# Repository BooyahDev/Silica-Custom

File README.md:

# SiliCa Custom — 4カード切替版

[19AJ137/SiliCa](https://github.com/19AJ137/SiliCa)を元に、4組のカード情報を外付けEEPROMへ保存し、4つのボタンで選択して応答する試作基板です。

回路・ファームウェアの修正、JLCPCB向けの標準0.3mmビアを使用した基板、製造データを収録しています。ボタンの動作、書込み、製造条件、検証結果は[詳細README](four_cards/README.md)を参照してください。

- 修正済みKiCadプロジェクト: `four_cards/cad/four_cards/`
- ファームウェアソース: `four_cards/src/1_1/`
- 書込み用HEXと手順: `four_cards/firmware/`
- 製造用Gerber: `four_cards/production/SiliCa_4cards_standard_via.zip`
- 実装部品表・配置: `four_cards/production/BOM.csv`、`CPL.csv`
- 検査報告: `four_cards/review/REVIEW.md`

基板5枚・5枚すべて上面実装を想定。DRCエラー・未配線0件、回路図の全77ピンと基板の接続一致を確認しています。RF応答、受動給電、EEPROM書込み時の電圧は実機未検証です。本設計は非暗号化応答の試作であり、任意のFeliCaカードの認証機能を代替するものではありません。

元リポジトリのライセンスは[UNLICENSE](UNLICENSE)です。

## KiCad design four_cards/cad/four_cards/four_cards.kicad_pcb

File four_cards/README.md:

# SiliCa — 4枚切替試作版

ATtiny1616を1個使い、4枚分のIDm・PMm・サービスコード・システムコード・12データブロックを、外付け24AA08に独立して保存する構成です。

- SW1〜SW4のうち1つを押している間だけ、そのカードが応答します。
- 未押下・複数同時押しでは応答しません。送信直前にも再確認します。
- カードを切り替えた最初の受信フレームは破棄して、選択カードの情報をRAMへ読み込みます。次のリーダのポーリングから応答します。読み込みには数十msを見込みますが実測は必要です。
- 4枚の保存先は256バイトずつの別バンクです。エラーログ32バイトはRAM内のみで、選択変更・電源断で消えます。
- ボタンは通信フレーム間と送信直前に判定します。通信フレームの送信を開始した後のリリースでは、そのフレームは完了します。

## ハードウェア

`cad/four_cards/four_cards.kicad_sch` と `four_cards.kicad_pcb` が変更後の回路図・基板です。80×50mmの元の外形とアンテナを維持し、上側に4つのスイッチを横並びに配置します。

| 部品 | 接続・仕様 |
| --- | --- |
| SW1 | PB2（U1 pin 12）—GND |
| SW2 | PB3（U1 pin 11）—GND |
| SW3 | PB4（U1 pin 10）—GND |
| SW4 | PB5（U1 pin 9）—GND |
| U2 | 24AA08T-I/SN（SOIC-8）、VCC/VSSは既存の整流電源 |
| U2 SDA / SCL | PA1（U1 pin 20）/ PA2（U1 pin 1） |
| U2 WP | GND。A0/A1/A2は内部未接続（基板ではGNDへ接続） |
| R4 / R5 | SDA / SCLの10kΩプルアップ |
| C5 | U2の電源デカップリング100nF |

追加配線は幅0.1mm、ビアはランド径0.45mm・ドリル径0.3mmを使用しています。JLCPCBの2層・1ozの仕様に合わせ、最小配線間隔0.1mm、穴対銅箔間隔0.2mm等のルールをプロジェクトに保存しました。最小ビア0.3mmを発注時に指定します。小径ビアの追加加工費を避けるため、IC周辺を引き直し、R1〜R3・C3/C4を右へ4mm移動しました。アンテナの銅箔配線は維持し、QFN露出パッドは表面配線でGNDへ接続しています。

スイッチはJLCPCB実装対象のXKB TS-1187A-B-A-B（C318884）です。メーカー寸法図に合わせ、パッド1.0×0.75mm、中心X=±3.0mm、Y=±1.875mmとしました。上側の端子1–2、下側の3–4がそれぞれ常時導通し、押すと上下がつながります。PB2〜PB5は内部プルアップを使用します。

PA1/PA2をEEPROMに使うため、従来のTxD/RxDはSDA/SCLに変更します。UARTデバッグは使えません。UPDIは従来のままです。

24AA08は1.7Vから使用でき、ソフトウェアI2Cは100kHz以下です。受動給電ではEEPROMの読み書きに必要な電流と電源保持時間が増えます。ネイティブKiCadのERC/DRCを実施し、エラーと未配線は0件です。書き込み中のVCC低下、RF応答時間、アンテナの同調は受領後に実機で確認してください。本版はその検証用試作です。

## ファームウェア・設定

```sh
cd src/1_1
pio run
```

24AA08には工場出荷時のカード情報はありません。各ボタンを押したまま、既存の`write.py`でそのカードを個別に設定します。例：

```sh
# SW1を押したまま、リーダ上で各コマンドを実行
python write.py idm 1122334455667788
python write.py sys ABCD
python write.py ser 000B
python write.py 0 00112233445566778899AABBCCDDEEFF
```

SW2〜SW4にも、それぞれ異なるIDmと必要なデータを設定してください。12ブロック全部を必要な内容に初期化します。書き込み完了表示までボタンを保持します。書き込み途中で給電が途切れるとページの内容が不完全になる可能性があるため、読み戻して確認します。元のマイコン内蔵EEPROMからの自動移行は行いません。

`RANDOMID`は選択時にRAM上で生成します。同じ選択を維持している間は同じIDmですが、再選択・再給電では変わり得ます。

## 検証

ATtiny1616向けPlatformIOビルド成功：RAM 1293 / 2048バイト（63.1%）、Flash 4599 / 16384バイト（28.1%）。

```sh
clang++ -std=c++11 -Wall -Wextra -fsanitize=address,undefined \
  -I src/1_1/src tests/cards_test.cpp src/1_1/src/application.cpp \
  -o /tmp/silica-cards-test
/tmp/silica-cards-test
```

ホストテストでは全ボタン組合せ、4つの保存バンクの分離、読み書き・再選択後の保持、IDm更新、未押下・別ボタン時の応答停止、メモリ書き込み失敗時の応答を確認しています。I2CとRFの実機動作はこのテストの対象外です。

`python tests/check_cad.py`では、KiCadファイル構文、追加30パッドの回路図と基板のネット一致、部品のインスタンス対応、PB2〜PB5の割当を確認しています。これはKiCadネイティブのERC/DRCの代替ではありません。

## 製造・書込みデータ

`production/SiliCa_4cards_standard_via.zip`、`production/BOM.csv`、`production/CPL.csv`が本版の製造データです。2層FR-4、80×50mm、厚さ1.6mm、銅厚1oz、上面実装18部品/枚。5枚すべてを実装します。U1の実装角度は、元のカスタムフットプリントのピン番号の向きに合わせ270°です。U2もJLCPCBの配置モデルに合わせ270°に修正し、左右の端子と左上のピン1マークの一致を確認しました。ダイオードはプレビュー詳細モデルがないため元CPLの180°を維持し、工場DFMで要照合です。

AE1は基板アンテナの端子表示、J1はUPDI接続用の未実装スルーホールです。外付けアンテナやJ1のピンヘッダは部品実装に含みません。書込み時にはJ1のUPDI/GND/VCCを使用してください。ファームウェアは`firmware/four_cards.hex`です。工場での書込みは依頼しません。

`fuses.c`のヒューズ値はFlash HEXに含まれません。Flashを書いて照合するだけではBOD等は設定されないため、書込みツールでヒューズも別途設定・読み戻してください。UPDIを無効化しないでください。具体的な値は`firmware/PROGRAMMING.md`を参照してください。

`tools/build_cad.py`と`tools/route_added.py`は初期試作の生成スクリプトです。本版の修正済みCADに対して再実行すると変更が失われるため、再生成せずKiCadファイルを編集してください。ローカル部品ライブラリを同梱しています。

## 参照

- 指定部品：https://www.switch-science.com/products/39
- スイッチ寸法図：https://cdn.sparkfun.com/assets/2/7/d/f/0/SMD-Button.pdf
- 24AA08データシート：https://ww1.microchip.com/downloads/en/DeviceDoc/24AA08-24LC08B-24FC08-8K-I2C-Serial-EEPROM-20001710N.pdf
- ATtiny1616データシート：https://ww1.microchip.com/downloads/en/DeviceDoc/ATtiny1614-16-17-DataSheet-DS40002204A.pdf

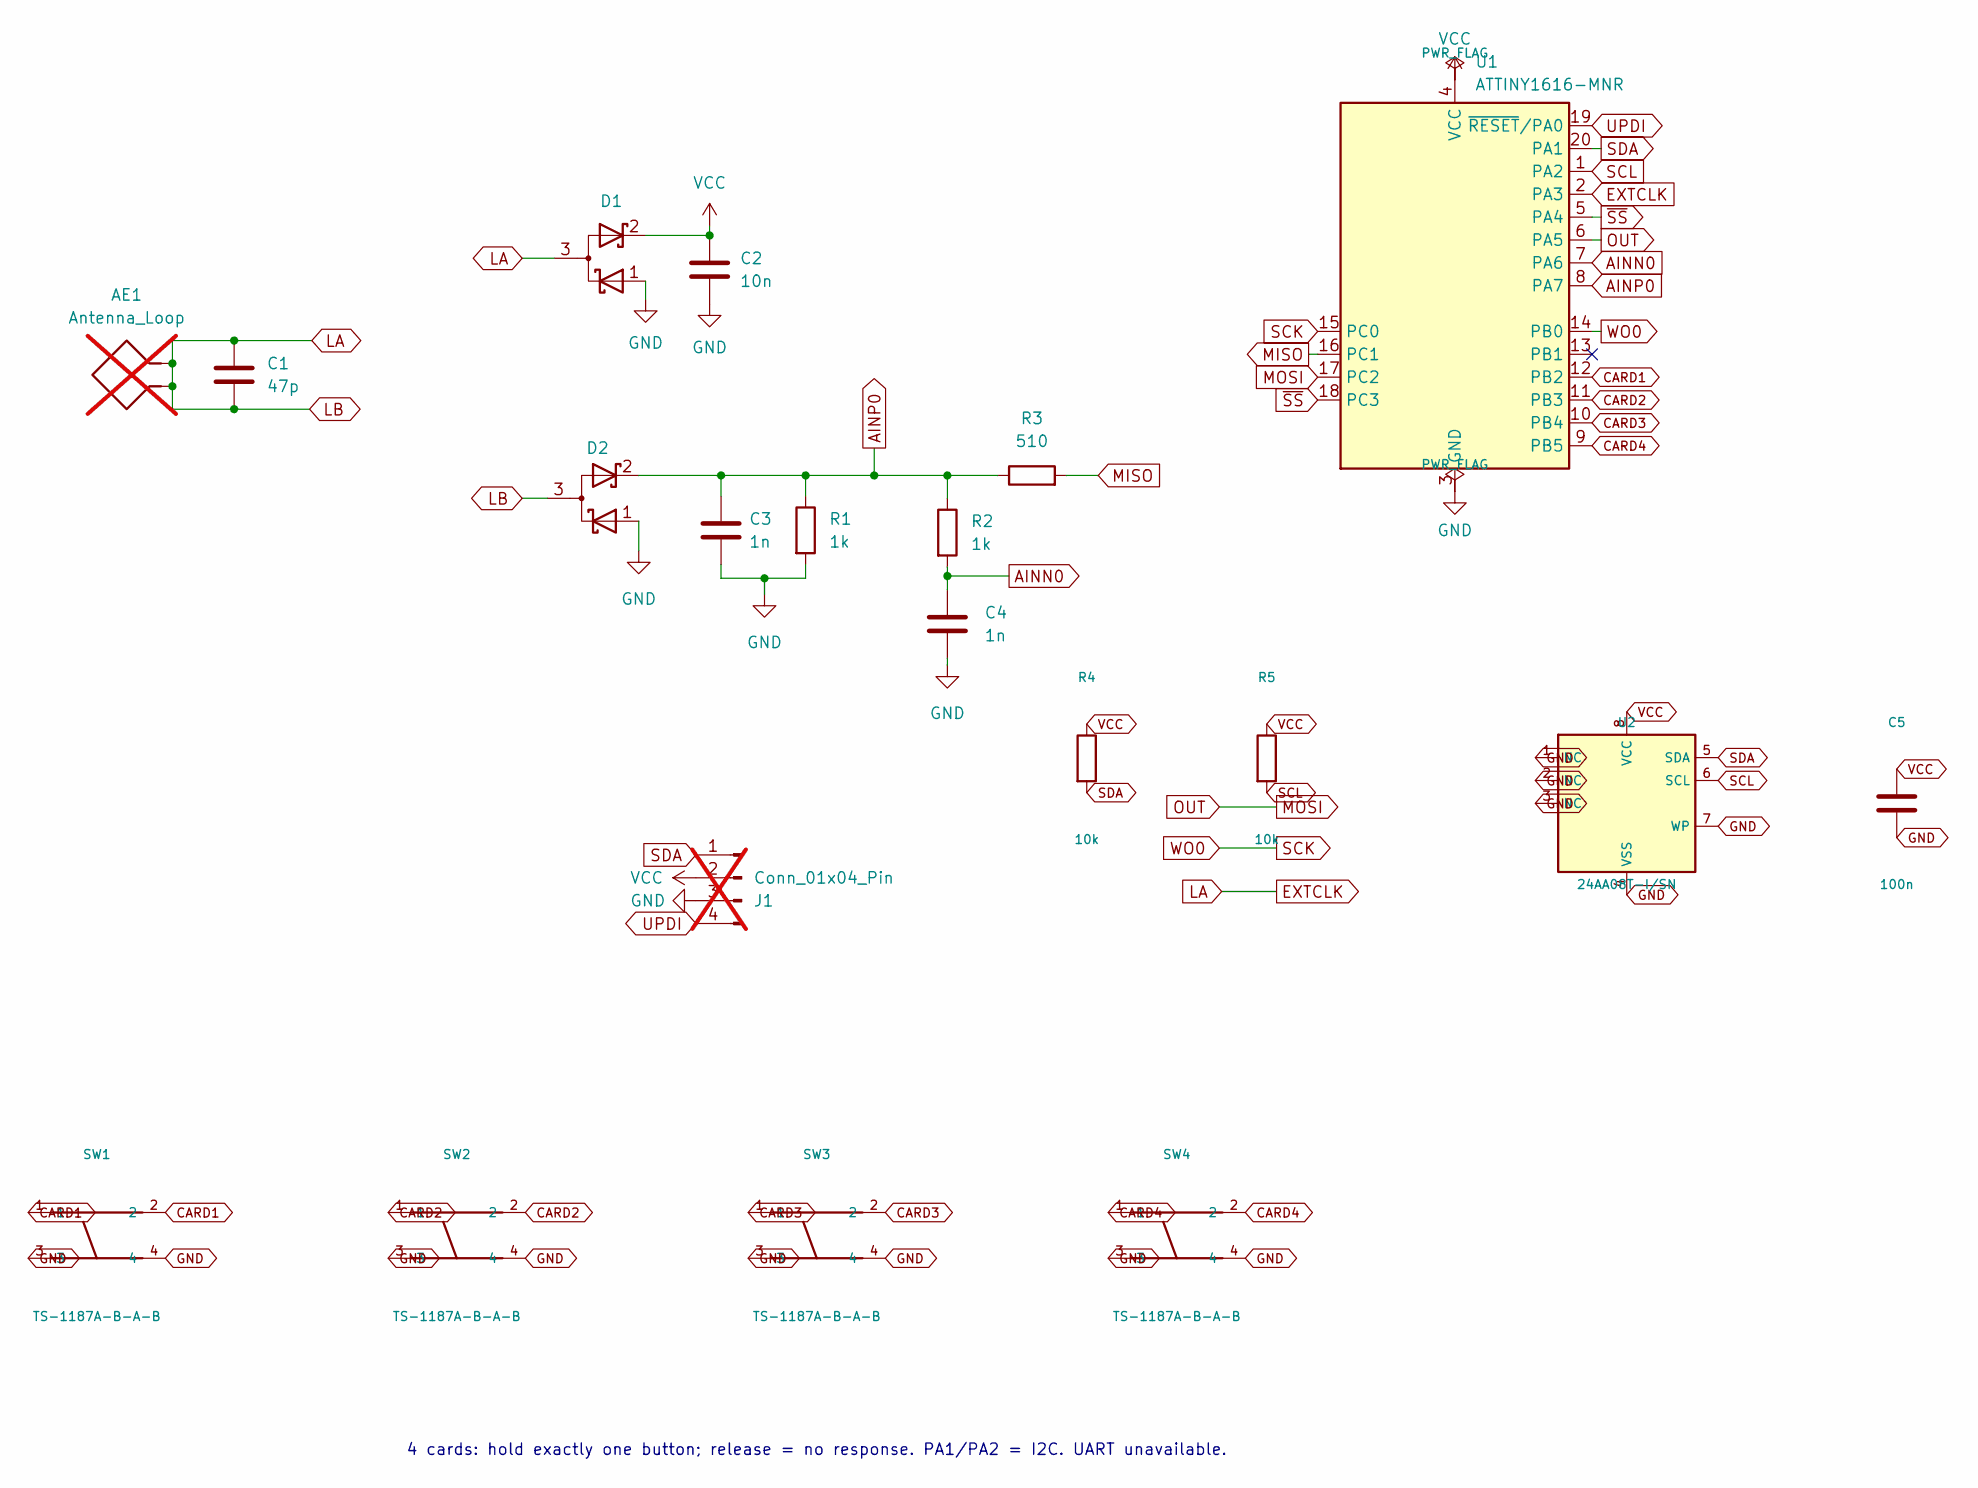
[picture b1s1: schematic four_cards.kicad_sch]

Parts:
AE1: Antenna_Loop; AE1; not fitted
C1: 47p; C1
C2: 10n; C2
C3: 1n; C3
C4: 1n; C4
C5: 100n; C5
D1: BAT54ST; D1
D2: BAT54ST; D2
J1: Conn_01x04_Pin; J1; not fitted
R1: 1k; R1
R2: 1k; R2
R3: 510; R3
R4: 10k; R4
R5: 10k; R5
SW1: TS-1187A-B-A-B; SW1
SW2: TS-1187A-B-A-B; SW2
SW3: TS-1187A-B-A-B; SW3
SW4: TS-1187A-B-A-B; SW4
U1: ATTINY1616-MNR; U1
U2: 24AA08T-I/SN; U2

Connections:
AINN0: C4.1, R2.2, U1.7 (PA6)
AINP0: C3.1, D2.2 (K), R1.1, R2.1, R3.1, U1.8 (PA7)
CARD1: SW1.1, SW1.2, U1.12 (PB2)
CARD2: SW2.1, SW2.2, U1.11 (PB3)
CARD3: SW3.1, SW3.2, U1.10 (PB4)
CARD4: SW4.1, SW4.2, U1.9 (PB5)
EXTCLK: AE1.1, AE1.2, C1.1, C1.2, D1.3 (A), D2.3 (A), U1.2 (PA3)
GND: C2.2, C3.2, C4.2, C5.2, D1.1 (K), D2.1 (K), J1.3, R1.2, SW1.3, SW1.4, SW2.3, SW2.4, SW3.3, SW3.4, SW4.3, SW4.4, U1.3 (GND), U1.21 (GND), U2.1 (NC), U2.2 (NC), U2.3 (NC), U2.4 (VSS), U2.7 (WP)
MISO: R3.2, U1.16 (PC1)
MOSI: U1.6 (PA5), U1.17 (PC2)
SCK: U1.14 (PB0), U1.15 (PC0)
SCL: R5.2, U1.1 (PA2), U2.6 (SCL)
SDA: J1.1, R4.2, U1.20 (PA1), U2.5 (SDA)
UPDI: J1.4, U1.19 (~RESET/PA0)
VCC: C2.1, C5.1, D1.2 (K), J1.2, R4.1, R5.1, U1.4 (VCC), U2.8 (VCC)
~SS: U1.5 (PA4), U1.18 (PC3)

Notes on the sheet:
4 cards: hold exactly one button; release = no response. PA1/PA2 = I2C. UART unavailable.

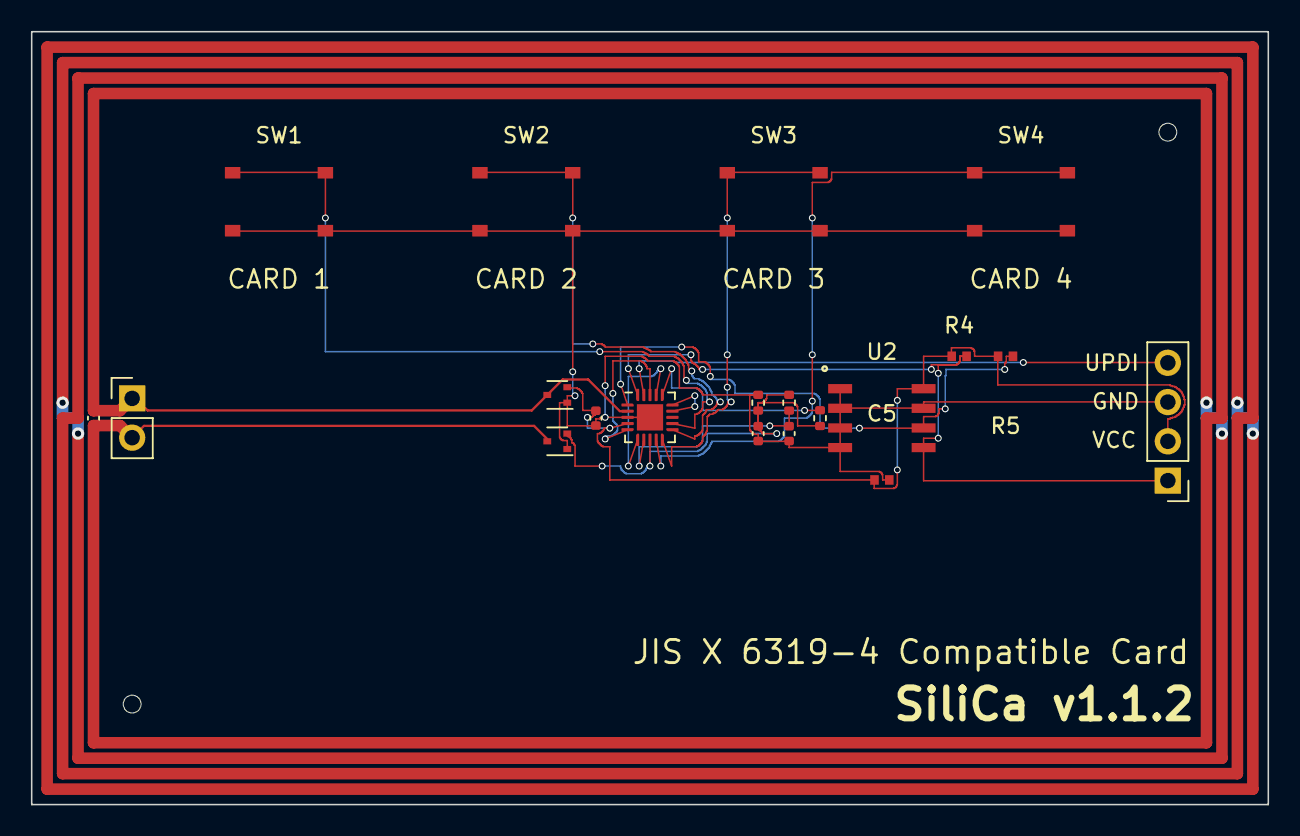
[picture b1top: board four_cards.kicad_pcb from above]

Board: 2 copper layers, 80.0 x 50.0 mm, 20 parts (0 on the bottom side), 16 nets.

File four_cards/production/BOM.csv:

Comment,Designator,Footprint,LCSC Part #
47pF,C1,0402,C1567
10nF,C2,0402,C15195
1nF,"C3,C4",0402,C1523
100nF,C5,0402,C1525
BAT54ST,"D1,D2",SOT-523,C2919808
1k,"R1,R2",0402,C11702
510,R3,0402,C25123
10k,"R4,R5",0402,C25744
TS-1187A-B-A-B,"SW1,SW2,SW3,SW4",6x3.5mm,C318884
ATTINY1616-MNR,U1,VQFN-20-EP_3x3mm,C507118
24AA08T-I/SN,U2,SOIC-8_3.9x4.9mm_P1.27mm,C2060935

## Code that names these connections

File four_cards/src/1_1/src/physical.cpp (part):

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  _PROTECTED_WRITE(CLKCTRL.MCLKCTRLB, CLKCTRL_PDIV_4X_gc | CLKCTRL_ENABLE_bm);

  // Set up the analog comparator with a 25mV hysteresis and enable output on
  // PA5
  PORTA.DIRSET = PIN5_bm;
  AC0.CTRLA = AC_OUTEN_bm | AC_HYSMODE_25mV_gc | AC_ENABLE_bm;

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  PORTA.DIRSET = PIN4_bm;
  PORTA.OUTCLR = PIN4_bm;

  // Configure SCK to operate at fclk/8 = 423.75kHz and output on PB0
  // Configure WO2 with a phase shift for CCL input
  PORTB.DIRSET = PIN0_bm;
  TCA0.SINGLE.CTRLA = 0;
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  EVSYS.ASYNCCH0 = EVSYS_ASYNCCH0_CCL_LUT0_gc;
  EVSYS.ASYNCUSER3 = EVSYS_ASYNCUSER0_ASYNCCH0_gc;

  // Configure CCL to generate a filtered modulation signal on PC1
  CCL.CTRLA = 0;
  CCL.LUT0CTRLA = 0;
  CCL.LUT0CTRLB = CCL_INSEL1_MASK_gc | CCL_INSEL0_MASK_gc;
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  CCL.LUT1CTRLA =
      CCL_CLKSRC_bm | CCL_FILTSEL0_bm | CCL_OUTEN_bm | CCL_ENABLE_bm;

  // PA1/PA2 are used by the card EEPROM (UART debug unavailable).

  // Set up TCB0 for delayed response (Polling command)
  // Timer will be started in receive_command after capture_frame
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
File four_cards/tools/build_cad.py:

from pathlib import Path
import re,uuid,math
BASE=Path(__file__).resolve().parents[1]
SRC=BASE/'cad'/'baseline'
OUT=BASE/'cad'/'four_cards'; OUT.mkdir(exist_ok=True)
def uid(): return str(uuid.uuid4())
def expr(s):
 tokens=re.findall(r'"(?:\\.|[^"\\])*"|[^\s()]+|[()]',s)
 stack=[]; root=None
 for t in tokens:
  if t=='(':
   a=[]
   if stack: stack[-1].append(a)
   else: root=a
   stack.append(a)
  elif t==')': stack.pop()
  else: stack[-1].append(t)
 assert not stack
 return root
def dump(a,depth=0):
 if not isinstance(a,list): return a
 if not any(isinstance(x,list) for x in a): return '('+' '.join(a)+')'
 lead=[];tail=[]
 for x in a:
  (tail if isinstance(x,list) else lead).append(x)
 return '('+' '.join(lead)+'\n'+'\n'.join('\t'*(depth+1)+dump(x,depth+1) for x in tail)+'\n'+'\t'*depth+')'
def child(a,k): return next(x for x in a if isinstance(x,list) and x[0]==k)
def children(a,k): return [x for x in a if isinstance(x,list) and x[0]==k]
def q(s): return '"'+s+'"'
def effect(size=1): return f'(effects (font (size {size} {size})))'
def label(net,x,y):return expr(f'(global_label "{net}" (shape bidirectional) (at {x} {y} 0) {effect()} (uuid "{uid()}"))')
sch=expr((SRC/'1_1.kicad_sch').read_text())
root=child(sch,'uuid')[1].strip('"')
for a in children(sch,'global_label'):
 if a[1]=='"TxD"': a[1]='"SDA"'
 if a[1]=='"RxD"': a[1]='"SCL"'
lib=child(sch,'lib_symbols')
def libsymbol(name,pins,body):
 out=f'(symbol "SiliCa:{name}" (pin_names (offset 0.5)) (in_bom yes) (on_board yes) (property "Reference" "U" (at 0 8 0) {effect()}) (property "Value" "{name}" (at 0 -8 0) {effect()}) (symbol "{name}_0_1" {body}) (symbol "{name}_1_1" '
 for number,net,x,y,angle,kind in pins:
  out+=f'(pin {kind} line (at {x} {y} {angle}) (length 2.54) (name "{net}" {effect()}) (number "{number}" {effect()}))'
 return expr(out+'))')
pushpins=[(1,'1',-7.62,2.54,0,'passive'),(2,'2',7.62,2.54,180,'passive'),(3,'3',-7.62,-2.54,0,'passive'),(4,'4',7.62,-2.54,180,'passive')]
body='(polyline (pts (xy -5.08 2.54) (xy 5.08 2.54)) (stroke (width 0.254) (type default)) (fill (type none))) (polyline (pts (xy -5.08 -2.54) (xy 5.08 -2.54)) (stroke (width 0.254) (type default)) (fill (type none))) (polyline (pts (xy 0 -2.54) (xy -1.5 1.5)) (stroke (width 0.254) (type default)) (fill (type none)))'
lib.append(libsymbol('KPT-1187B',pushpins,body))
mem_pins=[(1,'NC',-10.16,5.08,0,'passive'),(2,'NC',-10.16,2.54,0,'passive'),(3,'NC',-10.16,0,0,'passive'),(4,'VSS',0,-10.16,90,'power_in'),(5,'SDA',10.16,5.08,180,'bidirectional'),(6,'SCL',10.16,2.54,180,'input'),(7,'WP',10.16,-2.54,180,'input'),(8,'VCC',0,10.16,270,'power_in')]
lib.append(libsymbol('24AA08',mem_pins,'(rectangle (start -7.62 7.62) (end 7.62 -7.62) (stroke (width 0.254) (type default)) (fill (type background)))'))
instances={}
def instance(name,ref,value,fp,x,y,pins):
 u=uid();instances[ref]=u
 out=f'(symbol (lib_id "{name}") (at {x} {y} 0) (unit 1) (in_bom yes) (on_board yes) (dnp no) (uuid "{u}") (property "Reference" "{ref}" (at {x} {y-9} 0) {effect()}) (property "Value" "{value}" (at {x} {y+9} 0) {effect()}) (property "Footprint" "{fp}" (at {x} {y} 0) (effects (font (size 1 1)) (hide yes)))'
 for pin in pins:out+=f'(pin "{pin[0]}" (uuid "{uid()}"))'
 out+=f'(instances (project "four_cards" (path "/{root}" (reference "{ref}") (unit 1)))))'
 sch.append(expr(out))
for i in range(4):
 x=65+i*40;y=168;net=f'CARD{i+1}'
 instance('SiliCa:KPT-1187B',f'SW{i+1}','COM-08720','SiliCa:COM-08720',x,y,pushpins)
 for pin,n,px,py,a,k in pushpins: sch.append(label(net if pin in (1,2) else 'GND',x+px,y-py))
 # U1 PB2..PB5 pins on right, y = origin - library-y.
 sch.append(label(net,231.14,72.644+i*2.54))
instance('SiliCa:24AA08','U2','24AA08-I/SN','Package_SO:SOIC-8_3.9x4.9mm_P1.27mm',235,120,mem_pins)
for number,n,x,y,a,k in mem_pins:
 if k=='no_connect':
  sch.append(expr(f'(no_connect (at {235+x} {120-y}) (uuid "{uid()}"))'))
 else: sch.append(label({'VSS':'GND','WP':'GND','NC':'GND'}.get(n,n),235+x,120-y))
# Reuse the embedded standard resistor/capacitor symbols.
for name,ref,val,fp,x,y,pins,nets in [
 ('Device:R','R4','10k','Resistor_SMD:R_0402_1005Metric',175,115,[(1,'',0,3.81,270,'passive'),(2,'',0,-3.81,90,'passive')],['VCC','SDA']),
 ('Device:R','R5','10k','Resistor_SMD:R_0402_1005Metric',195,115,[(1,'',0,3.81,270,'passive'),(2,'',0,-3.81,90,'passive')],['VCC','SCL']),
 ('Device:C','C5','100n','Capacitor_SMD:C_0402_1005Metric',265,120,[(1,'',0,3.81,270,'passive'),(2,'',0,-3.81,90,'passive')],['VCC','GND'])]:
 instance(name,ref,val,fp,x,y,pins)
 for pin,net in zip(pins,nets): sch.append(label(net,x+pin[2],y-pin[3]))
sch.append(expr(f'(text "4 cards: hold exactly one button; release = no response. PA1/PA2 = I2C. UART unavailable." (at 145 192 0) {effect(1.27)} (uuid "{uid()}"))'))
(OUT/'four_cards.kicad_sch').write_text(dump(sch).replace('(project \"1_1\"', '(project \"four_cards\"')+'\n')
board=expr((SRC/'1_1.kicad_pcb').read_text())
for a in children(board,'net'):
 if a[2]=='"TxD"':a[2]='"SDA"'
 if a[2]=='"RxD"':a[2]='"SCL"'
 if 'unconnected-(U1-PB' in a[2]:
  m=re.search('PB([2345])',a[2])
  if m:a[2]=q('CARD'+str(int(m[1])-1))
nets={a[2].strip('"'):int(a[1]) for a in children(board,'net')}
# Rename all pad net labels and connector silk to reflect actual usage.
for fp in children(board,'footprint'):
 for pad in children(fp,'pad'):
  for a in children(pad,'net'):
   a[2]=q(next(k for k,v in nets.items() if v==int(a[1])))
for a in children(board,'gr_text'):
 if a[1]=='"TxD"':a[1]='"SDA"'
 if a[1]=='"RxD"':a[1]='"SCL"'
def footprint(lib,ref,val,x,y,pads,rect):
 s=f'(footprint "{lib}" (layer "F.Cu") (uuid "{uid()}") (at {x} {y}) (property "Reference" "{ref}" (at 0 -4.3 0) (layer "F.SilkS") {effect()}) (property "Value" "{val}" (at 0 4.3 0) (layer "F.Fab") {effect()}) (path "/{root}/{instances[ref]}") (attr smd)'
 a,b,c,d=rect
 s+=f'(fp_rect (start {a} {b}) (end {c} {d}) (stroke (width 0.15) (type default)) (fill none) (layer "F.SilkS"))'
 for num,px,py,w,h,net in pads:
  s+=f'(pad "{num}" smd rect (at {px} {py}) (size {w} {h}) (layers "F.Cu" "F.Paste" "F.Mask") (net {nets[net]} "{net}"))'
 board.append(expr(s+')'))
for i in range(4):
 net=f'CARD{i+1}'
 pads=[(1,-3.1,-1.85,1.8,1.1,net),(2,3.1,-1.85,1.8,1.1,net),(3,-3.1,1.85,1.8,1.1,'GND'),(4,3.1,1.85,1.8,1.1,'GND')]
 footprint('SiliCa:COM-08720',f'SW{i+1}','COM-08720',66+16*i,61,pads,(-2.6,-2.6,2.6,2.6))
 footprint_node=board[-1]
 board.append(expr(f'(gr_text "CARD {i+1}" (at {66+16*i} 66 0) (layer "F.SilkS") {effect(1.2)} (uuid "{uid()}"))'))
pads=[]
for n in range(1,9):
 side=-1 if n<=4 else 1
 py=(-1.905+(n-1)*1.27) if n<=4 else (1.905-(n-5)*1.27)
 net={1:'GND',2:'GND',3:'GND',4:'GND',5:'SDA',6:'SCL',7:'GND',8:'VCC'}[n]
 pads.append((n,side*2.7,py,1.55,0.6,net))
footprint('Package_SO:SOIC-8_3.9x4.9mm_P1.27mm','U2','24AA08',105,75,pads,(-1.95,-2.45,1.95,2.45))
for ref,val,x,y,na,nb,lib in [('R4','10k',110,71,'VCC','SDA','Resistor_SMD:R_0402_1005Metric'),('R5','10k',113,71,'VCC','SCL','Resistor_SMD:R_0402_1005Metric'),('C5','100n',105,79,'VCC','GND','Capacitor_SMD:C_0402_1005Metric')]:
 footprint(lib,ref,val,x,y,[(1,-0.48,0,0.56,0.62,na),(2,0.48,0,0.56,0.62,nb)],(-0.18,-0.45,0.18,0.45))
# Placement and connectivity are explicit; route the added nets in KiCad.
board.append(expr(f'(gr_text "4-CARD PROTOTYPE / ADDED NETS REQUIRE ROUTING" (at 90 86 0) (layer "User.1") {effect()} (uuid "{uid()}"))'))
(OUT/'four_cards.kicad_pcb').write_text(dump(board)+'\n')
# Local footprint based directly on manufacturer KPT-1187B land drawing.
pretty=OUT/'SiliCa.pretty';pretty.mkdir(exist_ok=True)
switch=next(f for f in children(board,'footprint') if child(f,'property')[2]=='"SW1"')
standalone=[a for a in switch if not(isinstance(a,list) and a[0] in ('at','path','uuid','property'))]
standalone[1]='"COM-08720"'
for pad in children(standalone,'pad'):
 pad[:]=[a for a in pad if not(isinstance(a,list) and a[0]=='net')]
standalone.insert(2,['version','20241229']);standalone.insert(3,['generator','"pcbnew"'])
(pretty/'COM-08720.kicad_mod').write_text(dump(standalone)+'\n')
(OUT/'fp-lib-table').write_text('(fp_lib_table (version 7) (lib (name "SiliCa") (type "KiCad") (uri "${KIPRJMOD}/SiliCa.pretty") (options "") (descr "COM-08720 manufacturer land drawing")))\n')
print('Created native schematic + PCB placement; added nets are unrouted.')
